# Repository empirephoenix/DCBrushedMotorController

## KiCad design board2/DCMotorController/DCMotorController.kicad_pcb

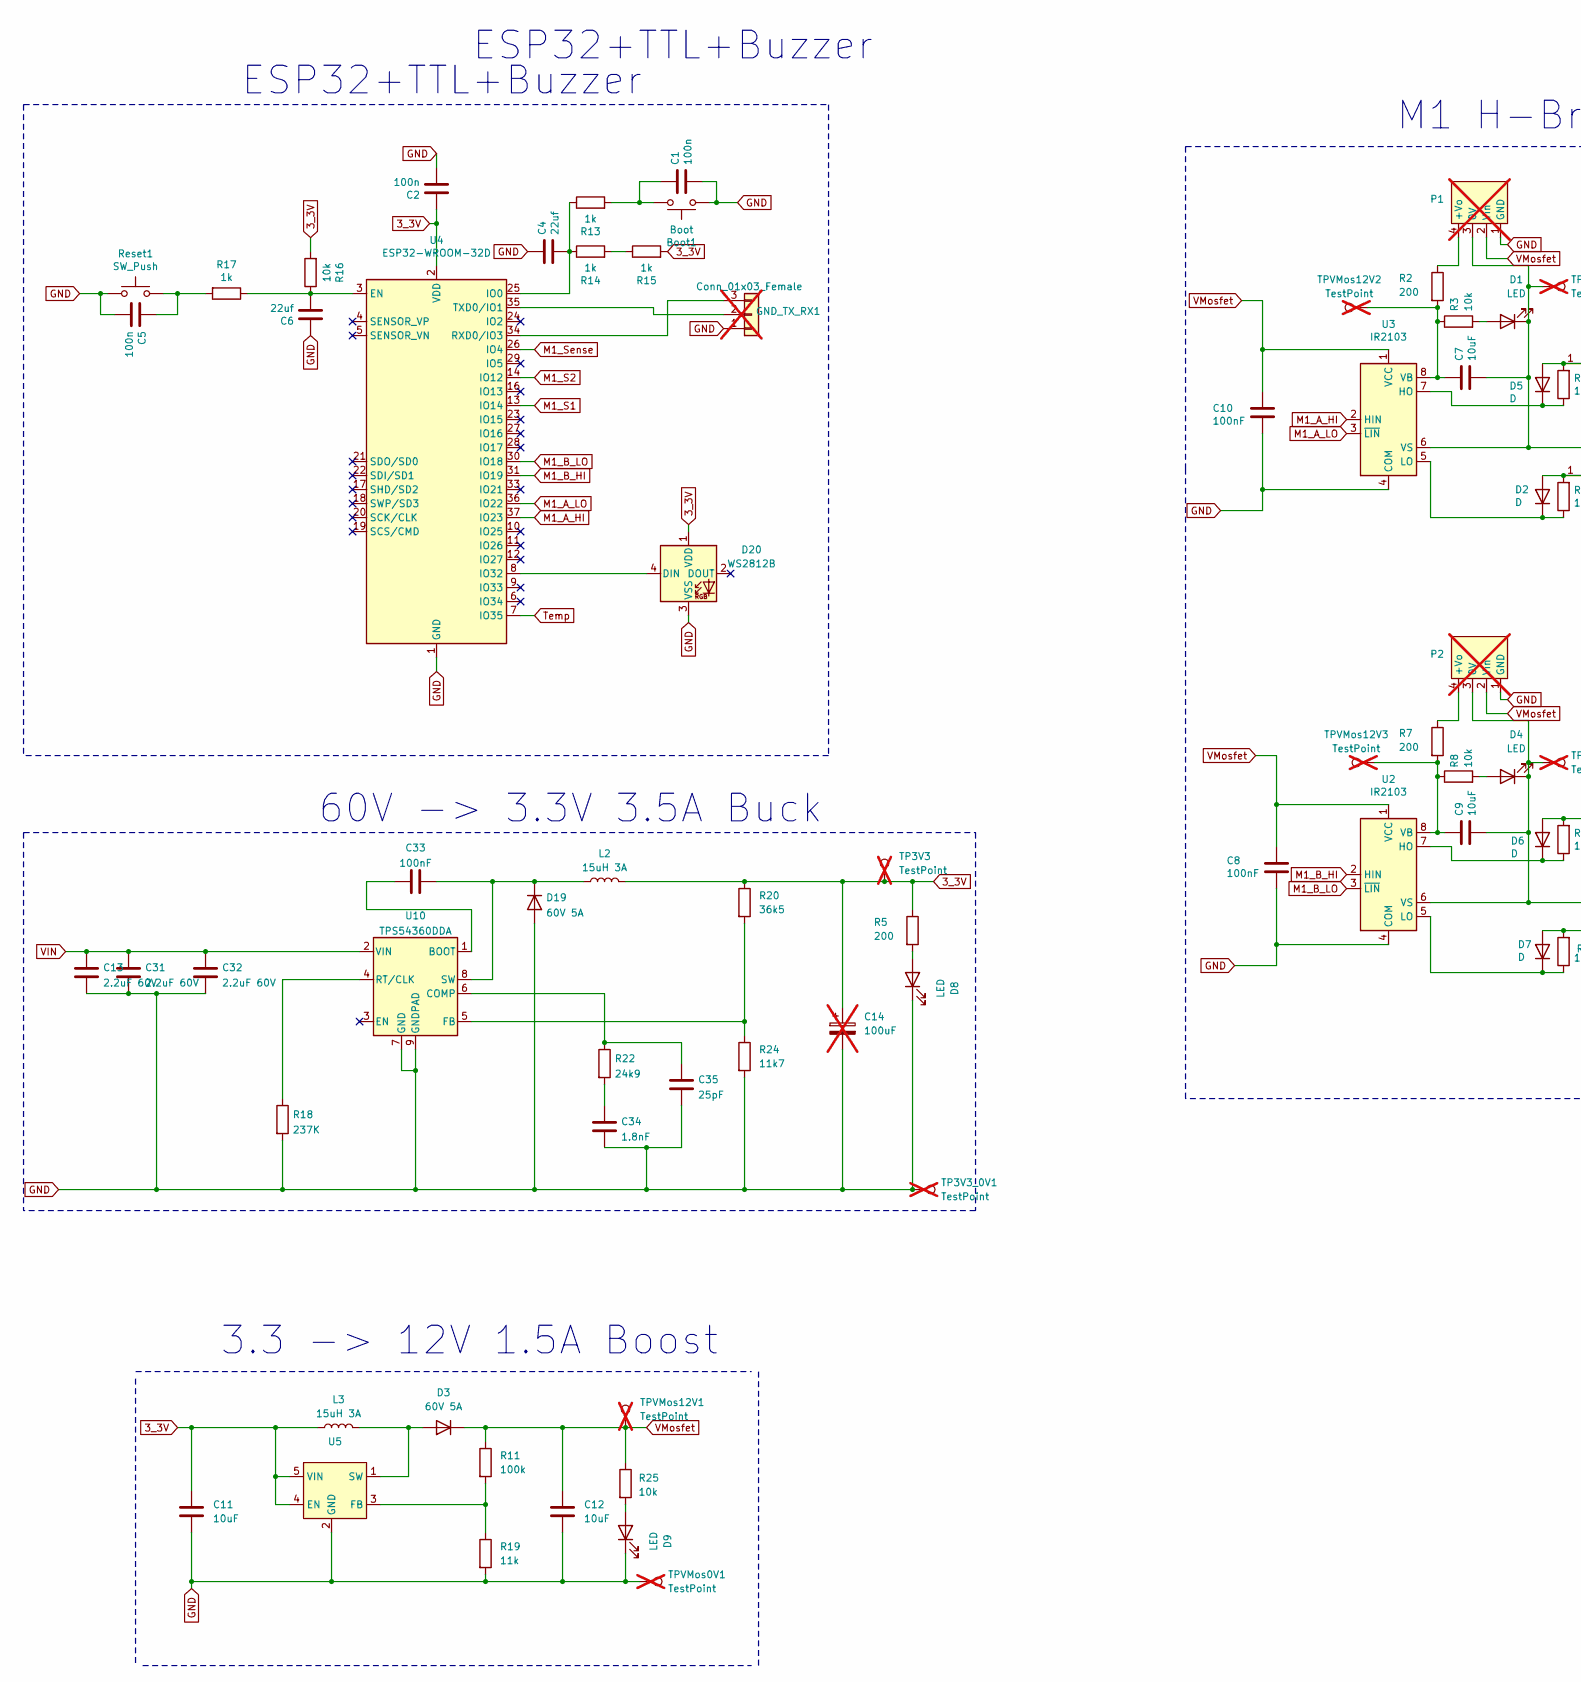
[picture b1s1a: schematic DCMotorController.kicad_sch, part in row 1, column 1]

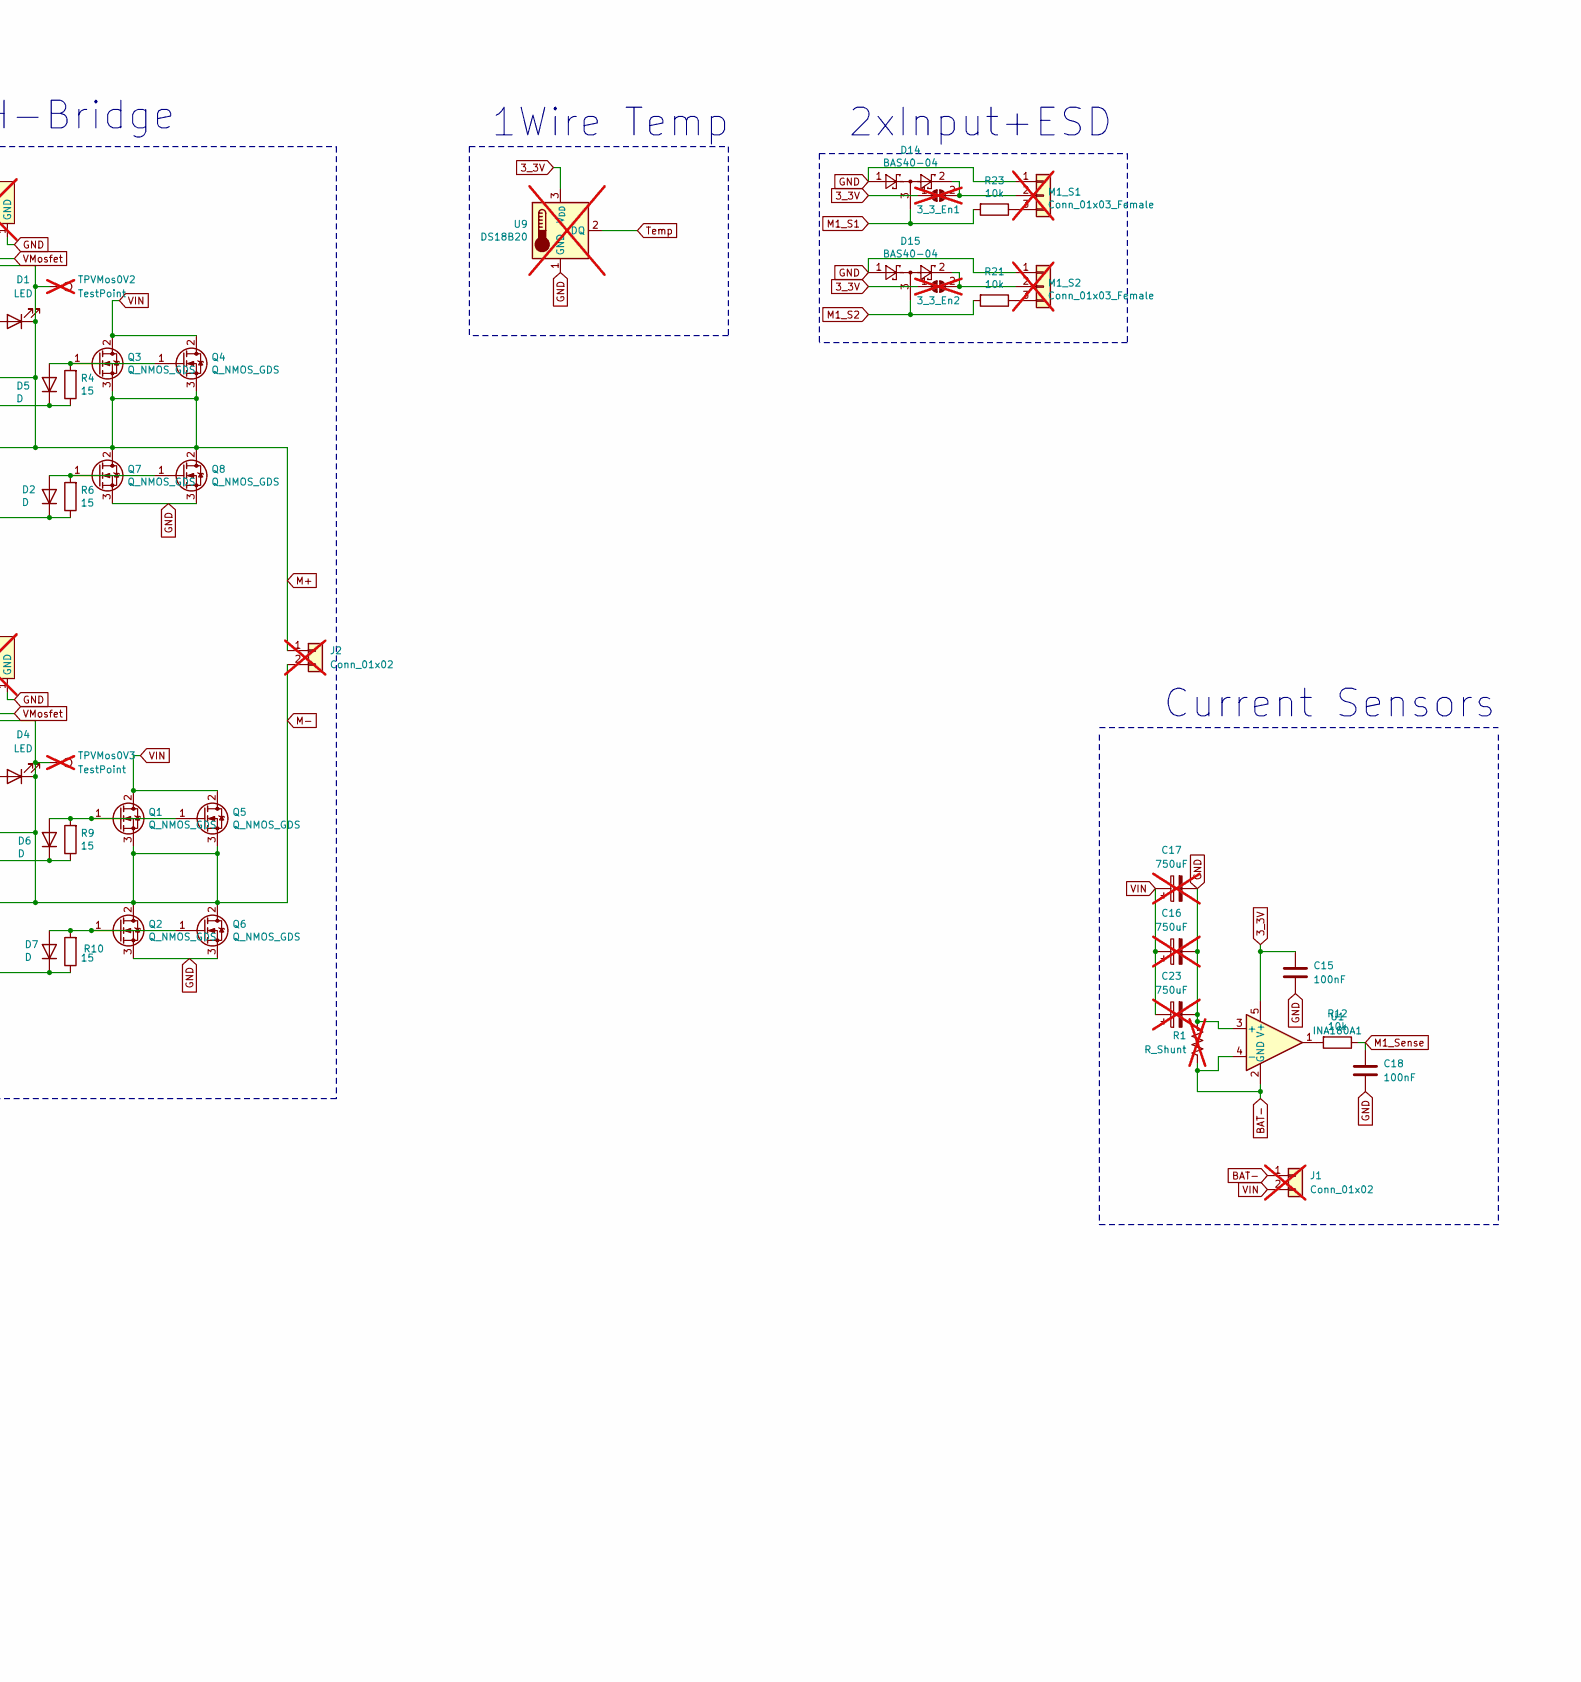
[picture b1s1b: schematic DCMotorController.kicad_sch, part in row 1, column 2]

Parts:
3_3_En1, 3_3_En2: SolderJumper-2_P1.3mm_Open_RoundedPad1.0x1.5mm; not fitted
Boot1: Boot; SW_SPST_CK_RS282G05A3; LCSC C72443
C1, C2, C5: 100n; C_0603_1608Metric; LCSC C14663
C4, C6: 22uf; C_0805_2012Metric; LCSC C5674
C7, C9: 10uF; C_1206_3216Metric; LCSC C13585
C8, C10, C15, C18, C33: 100nF; C_0603_1608Metric; LCSC C14663
C11, C12: 10uF; C_1206_3216Metric
C13, C31, C32: 2.2uF 60V; C_1206_3216Metric; LCSC C920964
C14: 100uF; CP_Radial_D10.0mm_P2.50mm_P5.00mm; not fitted
C16, C17, C23: 750uF; CP_Radial_D12.5mm_P5.00mm; LCSC C316460; not fitted
C34: 1.8nF; C_0603_1608Metric; LCSC C1599
C35: 25pF; C_0603_1608Metric; LCSC C282067
D1, D4, D8, D9: LED; LED_0805_2012Metric
D2, D5, D6, D7: D; D_SOD-123; LCSC C81598
D3, D19: 60V 5A; D_SMA; LCSC C513479
D14, D15: BAS40-04; SOT-23; LCSC C397601
D20: WS2812B; LED_WS2812B_PLCC4_5.0x5.0mm_P3.2mm; LCSC no
GND_TX_RX1: Conn_01x03_Female; PinHeader_1x03_P2.54mm_Vertical; LCSC no; not fitted
J1: Conn_01x02; AMASS_XT60-M_1x02_P7.20mm_Vertical; not fitted
J2: Conn_01x02; AMASS_XT60-F_1x02_P7.20mm_Vertical; not fitted
L2, L3: 15uH 3A; L_10.4x10.4_H4.8; LCSC C151872
M1_S1, M1_S2: Conn_01x03_Female; PinHeader_1x03_P2.54mm_Vertical; LCSC no; not fitted
P1, P2: Converter_DCDC_TRACO_TEA1-xxxx_THT; LCSC C7465190; not fitted
Q1, Q2, Q3, Q4, Q5, Q6, Q7, Q8: Q_NMOS_GDS; TO-252-2; LCSC C110912
R1: R_Shunt; Shunt 1moh 5W; LCSC C695947; not fitted
R2, R5, R7: 200; R_0603_1608Metric; LCSC C25217
R3, R8, R25: 10k; R_0603_1608Metric
R4, R6, R9, R10: 15; R_0603_1608Metric; LCSC C22810
R11: 100k; R_0603_1608Metric; LCSC C22797
R12, R16, R21, R23: 10k; R_0603_1608Metric; LCSC C25804
R13, R14, R15, R17: 1k; R_0603_1608Metric; LCSC C21190
R18: 237K; R_0603_1608Metric_Pad0.98x0.95mm_HandSolder; LCSC C2998117
R19: 11k; R_0603_1608Metric; LCSC C25950
R20: 36k5; R_0603_1608Metric; LCSC C2930095
R22: 24k9; R_0603_1608Metric; LCSC C25962
R24: 11k7; R_0805_2012Metric; LCSC C865154
Reset1: SW_Push; SW_SPST_CK_RS282G05A3; LCSC C72443
TP3V3, TP3V3_0V1: TestPoint; TestPoint_Pad_2.0x2.0mm; not fitted
TPVMos0V1, TPVMos0V2, TPVMos0V3, TPVMos12V1, TPVMos12V2, TPVMos12V3: TestPoint; TestPoint_Pad_2.0x2.0mm; not fitted
U1: INA180A1; SOT-23-5; LCSC C122228
U2, U3: IR2103; SOP-8_3.9x4.9mm_P1.27mm; LCSC C111908
U4: ESP32-WROOM-32D; ESP32-WROOM-32_no_wifi; LCSC C529578
U5: SOT-23-5; LCSC C181744
U9: DS18B20; TO-92_Inline; LCSC lcsc; not fitted
U10: TPS54360DDA; TI_SO-PowerPAD-8_ThermalVias; LCSC C44377

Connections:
3_3V: 3_3_En1.1 (A), 3_3_En2.1 (A), C2.2, C11.1, C14.1, C15.1, D20.1 (VDD), L2.2, L3.1, R5.1, R15.2, R16.2, R20.1, TP3V3.1, U1.5 (V+), U4.2 (VDD), U5.4 (EN), U5.5 (VIN), U9.3 (V_{DD})
BAT-: J1.1, R1.2, U1.2 (GND), U1.4 (-)
GND: Boot1.1, C1.1, C2.1, C4.1, C5.1, C6.1, C8.2, C10.2, C11.2, C12.2, C13.2, C14.2, C15.2, C16.2, C17.2, C18.1, C23.2, C31.2, C32.2, C34.2, C35.2, D8.1 (K), D9.1 (K), D14.1, D15.1, D19.2 (A), D20.3 (VSS), GND_TX_RX1.1, M1_S1.1, M1_S2.1, P1.1 (GND), P2.1 (GND), Q2.3 (S), Q6.3 (S), Q7.3 (S), Q8.3 (S), R1.1, R18.2, R19.2, R24.2, Reset1.1, TP3V3_0V1.1, TPVMos0V1.1, U1.3 (+), U2.4 (COM), U3.4 (COM), U4.1 (GND), U4.15 (GND), U4.38 (GND), U4.39 (GND), U5.2 (GND), U9.1 (GND), U10.7 (GND), U10.9 (GNDPAD)
M1_A_HI: U3.2 (HIN), U4.37 (IO23)
M1_A_LO: U3.3 (~LIN), U4.36 (IO22)
M1_B_HI: U2.2 (HIN), U4.31 (IO19)
M1_B_LO: U2.3 (~LIN), U4.30 (IO18)
M1_S1: D14.3, R23.2, U4.13 (IO14)
M1_S2: D15.3, R21.2, U4.14 (IO12)
M1_Sense: C18.2, R12.1, U4.26 (IO4)
M+: C7.2, D1.1 (K), J2.1, P1.3 (0V), Q3.3 (S), Q4.3 (S), Q7.2 (D), Q8.2 (D), TPVMos0V2.1, U3.6 (VS)
M-: C9.2, D4.1 (K), J2.2, P2.3 (0V), Q1.3 (S), Q2.2 (D), Q5.3 (S), Q6.2 (D), TPVMos0V3.1, U2.6 (VS)
unnamed: 3_3_En1.2 (B), D14.2, M1_S1.2
unnamed: 3_3_En2.2 (B), D15.2, M1_S2.2
unnamed: Boot1.2, C1.2, R13.2
unnamed: C5.2, R17.2, Reset1.2
unnamed: C34.1, R22.2
unnamed: D1.2 (A), R3.2
unnamed: D2.2 (A), Q7.1 (G), Q8.1 (G), R6.2
unnamed: D2.1 (K), R6.1, U3.5 (LO)
unnamed: D3.2 (A), L3.2, U5.1 (SW)
unnamed: D4.2 (A), R8.2
unnamed: D5.2 (A), Q3.1 (G), Q4.1 (G), R4.2
unnamed: D5.1 (K), R4.1, U3.7 (HO)
unnamed: D6.2 (A), Q1.1 (G), Q5.1 (G), R9.2
unnamed: D6.1 (K), R9.1, U2.7 (HO)
unnamed: D7.2 (A), Q2.1 (G), Q6.1 (G), R10.2
unnamed: D7.1 (K), R10.1, U2.5 (LO)
unnamed: D8.2 (A), R5.2
unnamed: D9.2 (A), R25.2
unnamed: C33.2, D19.1 (K), L2.1, U10.8 (SW)
unnamed: D20.4 (DIN), U4.8 (IO32)
unnamed: GND_TX_RX1.2, U4.35 (TXD0/IO1)
unnamed: GND_TX_RX1.3, U4.34 (RXD0/IO3)
unnamed: M1_S1.3, R23.1
unnamed: M1_S2.3, R21.1
unnamed: P1.4 (+Vo), R2.1
unnamed: P2.4 (+Vo), R7.1
unnamed: R12.2, U1.1
unnamed: R14.2, R15.1
unnamed: C9.1, R7.2, R8.1, TPVMos12V3.1, U2.8 (VB)
unnamed: C7.1, R2.2, R3.1, TPVMos12V2.1, U3.8 (VB)
unnamed: C6.2, R16.1, R17.1, U4.3 (EN)
unnamed: C4.2, R13.1, R14.1, U4.25 (IO0)
unnamed: R11.2, R19.1, U5.3 (FB)
unnamed: C33.1, U10.1 (BOOT)
unnamed: C35.1, R22.1, U10.6 (COMP)
unnamed: R20.2, R24.1, U10.5 (FB)
unnamed: R18.1, U10.4 (RT/CLK)
Temp: U4.7 (IO35), U9.2 (DQ)
VIN: C13.1, C16.1, C17.1, C23.1, C31.1, C32.1, J1.2, Q1.2 (D), Q3.2 (D), Q4.2 (D), Q5.2 (D), U10.2 (VIN)
VMosfet: C8.1, C10.1, C12.1, D3.1 (K), P1.2 (Vin), P2.2 (Vin), R11.1, R25.1, TPVMos12V1.1, U2.1 (VCC), U3.1 (VCC)

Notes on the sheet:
Current Sensors
3.3 -> 12V 1.5A Boost
60V -> 3.3V 3.5A Buck
ESP32+TTL+Buzzer
1Wire Temp
2xInput+ESD
M1 H-Bridge

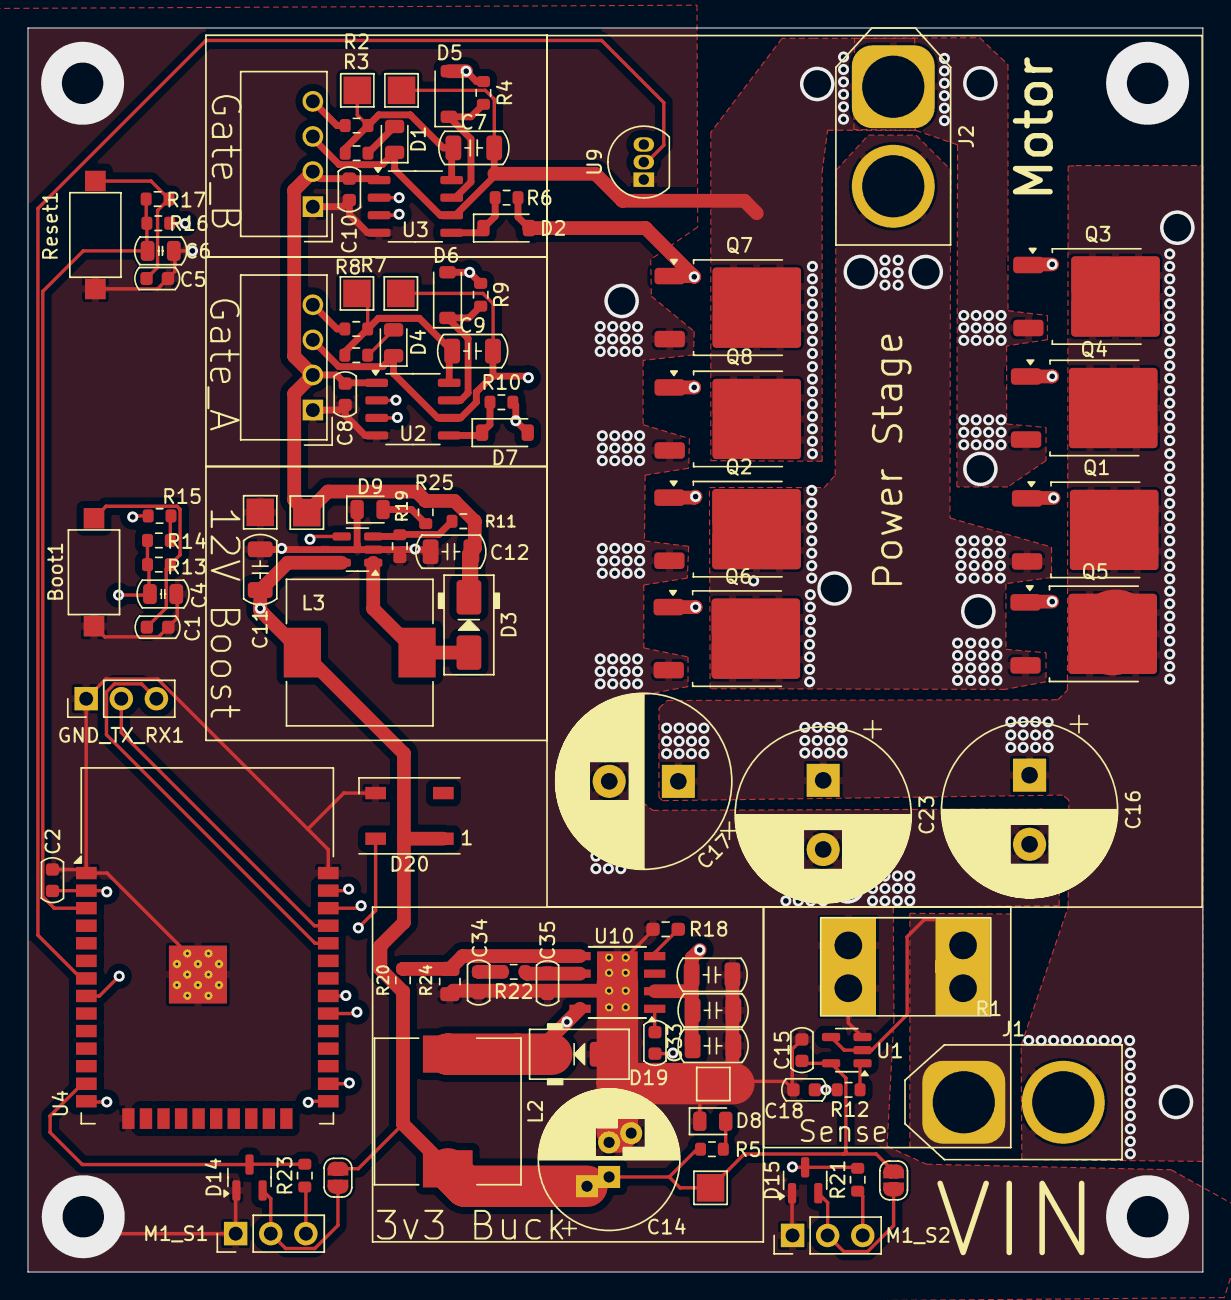
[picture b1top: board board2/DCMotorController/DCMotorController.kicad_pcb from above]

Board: 4 copper layers, 85.0 x 90.0 mm, 97 parts (0 on the bottom side), 52 nets.

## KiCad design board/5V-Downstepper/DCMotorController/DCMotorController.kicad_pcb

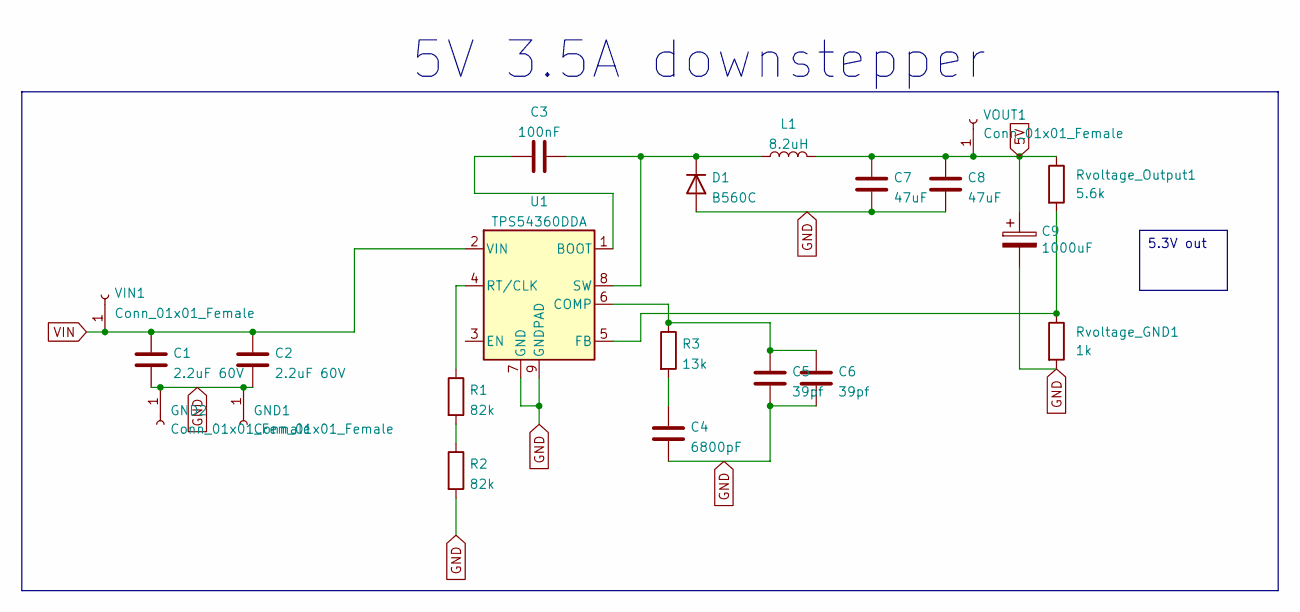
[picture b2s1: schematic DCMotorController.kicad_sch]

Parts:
C1, C2: 2.2uF 60V; C_1206_3216Metric; LCSC C920964
C3: 100nF; C_0603_1608Metric; LCSC C14663
C4: 6800pF; C_0603_1608Metric; LCSC C1631
C5, C6: 39pf; C_0603_1608Metric; LCSC C1666
C7, C8: 47uF; C_1206_3216Metric; LCSC C96123
C9: 1000uF; CP_Radial_D10.0mm_P5.00mm; LCSC C503217
D1: B560C; D_SMC_Handsoldering; LCSC C85100
GND1, GND2: Conn_01x01_Female; 60A_Wire_solder
L1: 8.2uH; L_12x12mm_H8mm; LCSC C2761921
R1, R2: 82k; R_0603_1608Metric_Pad0.98x0.95mm_HandSolder; LCSC C23254
R3: 13k; R_0603_1608Metric; LCSC C22797
Rvoltage_GND1: 1k; R_0603_1608Metric
Rvoltage_Output1: 5.6k; R_0603_1608Metric
U1: TPS54360DDA; TI_SO-PowerPAD-8_ThermalVias; LCSC C44377
VIN1: Conn_01x01_Female; 60A_Wire_solder
VOUT1: Conn_01x01_Female; 60A_Wire_solder

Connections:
5V: C7.1, C8.1, C9.1, L1.2, Rvoltage_Output1.1, VOUT1.1
GND: C1.2, C2.2, C4.2, C5.2, C6.2, C7.2, C8.2, C9.2, D1.2 (A), GND1.1, GND2.1, R2.2, Rvoltage_GND1.2, U1.7 (GND), U1.9 (GNDPAD)
unnamed: C3.1, U1.1 (BOOT)
unnamed: C3.2, D1.1 (K), L1.1, U1.8 (SW)
unnamed: C4.1, R3.2
unnamed: C5.1, C6.1, R3.1, U1.6 (COMP)
unnamed: R1.1, U1.4 (RT/CLK)
unnamed: R1.2, R2.1
unnamed: Rvoltage_GND1.1, Rvoltage_Output1.2, U1.5 (FB)
VIN: C1.1, C2.1, U1.2 (VIN), VIN1.1

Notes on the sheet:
5.3V out
5V 3.5A downstepper

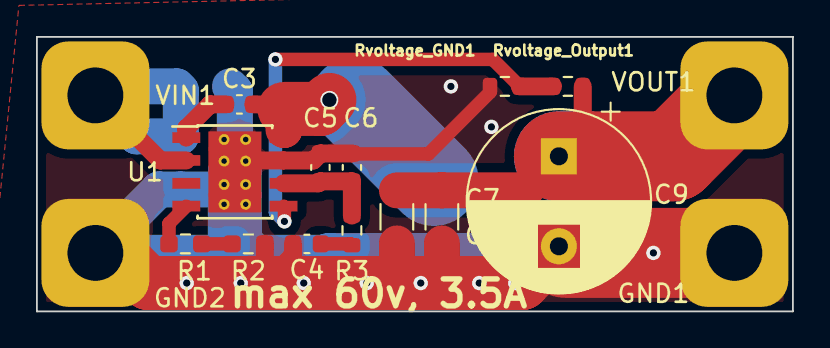
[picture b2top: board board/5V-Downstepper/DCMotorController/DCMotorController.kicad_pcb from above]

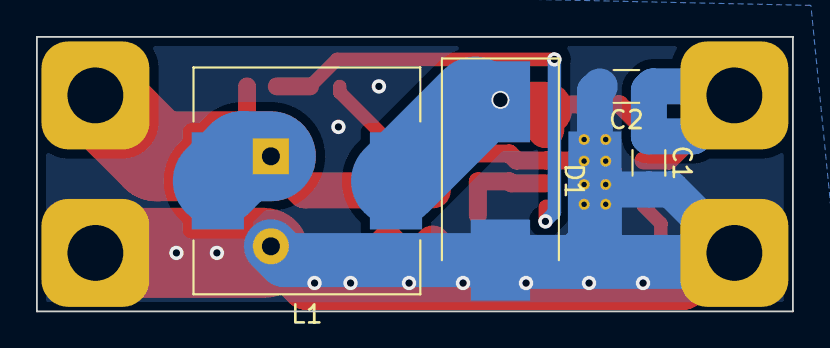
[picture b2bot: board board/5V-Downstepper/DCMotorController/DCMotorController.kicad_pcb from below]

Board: 2 copper layers, 42.0 x 15.2 mm, 21 parts (4 on the bottom side), 10 nets.

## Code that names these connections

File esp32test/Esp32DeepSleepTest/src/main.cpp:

#include <Arduino.h>
#include <Adafruit_NeoPixel.h>
#include "joy_rmt_rc.h"
#include "RunningMedian.h"
#include <OneWire.h>
#include <DallasTemperature.h>

// pin setup
#define LED_STATUS 32
#define ONE_WIRE_BUS 35

#define M1_SENSE 4

#define IN1 14
#define IN2 12

#define M1_A_LO 22
#define M1_A_HI 23
#define M1_B_LO 18
#define M1_B_HI 19

#define freq 6000
#define resolution 8

// Configuration
#define SHUNT_MOHM 2
#define MAX_AVG_CURRENT 15000
#define MAX_SPIKE_CURRENT 60000
#define NULL_PASS_DELAY 50

#define mode 0
#define turningMod 0

#define deadzoneMinCH1 1480
#define deadzoneMaxCH1 1520
#define minCH1 950
#define maxCH1 2050

#define minTEMPC -30
#define maxTEMPC 60

// constants
#define STATE_WAIT_NEUTRAL 0
#define STATE_DEFAULT 1
#define STATE_ERROR -1

#define FOREACH_INPUT(INPUT) \
  INPUT(NONE)                \
  INPUT(RC)                  \
  INPUT(VOLTAGE)

#define GENERATE_ENUM(ENUM) ENUM,
#define GENERATE_STRING(STRING) #STRING,

enum INPUT_MODE
{
  FOREACH_INPUT(GENERATE_ENUM)
};

Adafruit_NeoPixel pixels(1, LED_STATUS, NEO_GRBW);

float lastPower;
float nullPass;

const int M1_A_CHANNEL = 0;
const int M1_B_CHANNEL = 1;

RunningMedian m1 = RunningMedian(10);
long m1_last = 0;
  int state = STATE_WAIT_NEUTRAL;

// Configure RMT peripheral for each RC channel
RingbufHandle_t ringbuffers[axis_count];

void check(bool value, char *output)
{
  if (value)
  {
    printf(output);
  }
}

void setup()
{
  lastPower = 0;
  Serial.begin(115200);

  pinMode(IN1, INPUT);
  pinMode(IN2, INPUT);

  pinMode(M1_A_LO, OUTPUT);
  pinMode(M1_A_HI, OUTPUT);
  pinMode(M1_B_LO, OUTPUT);
  pinMode(M1_B_HI, OUTPUT);
 
  yield();
  
  pixels.begin();
  pixels.setPixelColor(0, pixels.Color(0, 10, 0));
  pixels.show();
  Serial.println("Start done");

  pixels.setPixelColor(0, pixels.Color(100, 0, 0));
  pixels.show();


  ledcSetup(M1_A_CHANNEL, freq, resolution);
  ledcAttachPin(M1_A_HI, M1_A_CHANNEL);
  ledcSetup(M1_B_CHANNEL, freq, resolution);
  ledcAttachPin(M1_B_HI, M1_B_CHANNEL);

  esp_err_t er = ESP_OK;
  for (int i = 0; i < axis_count; i++)
  {
    rmt_config_t rmt_rx_config = {};
    rmt_rx_config.rmt_mode = RMT_MODE_RX;
    rmt_rx_config.channel = rc_channels[i].channel;
    rmt_rx_config.clk_div = rmt_clock_divider;
    rmt_rx_config.gpio_num = rc_channels[i].pin;
    rmt_rx_config.mem_block_num = 1;
    rmt_rx_config.rx_config.filter_en = true;
    rmt_rx_config.rx_config.filter_ticks_thresh = rmt_filter_threshold;
    rmt_rx_config.rx_config.idle_threshold = rmt_idle_threshold;

    er = rmt_config(&rmt_rx_config);
    check(ESP_OK != er, "ERROR: rmt_config failed\n");

    er = rmt_driver_install(rc_channels[i].channel, 1024, 0);
    check(ESP_OK != er, "ERROR: rmt_driver_install failed\n");

    er = rmt_get_ringbuf_handle(rc_channels[i].channel, &(ringbuffers[i]));
    check(ESP_OK != er, "ERROR: rmt_get_ringbuf_handle failed\n");
    check(NULL == ringbuffers[i], "ERROR: rmt_get_ringbuf_handle gave a NULL handle\n");

    er = rmt_rx_start(rc_channels[i].channel, true);
    check(ESP_OK != er, "ERROR: rmt_rx_start failed\n");
  }

  pixels.setPixelColor(0, pixels.Color(0, 0, 100));
  pixels.show();
}

float mapfloat(float x, float in_min, float in_max, float out_min, float out_max)
{
  return (x - in_min) * (out_max - out_min) / (in_max - in_min) + out_min;
}

void joy_rmt_rc_read_task()
{

  // Read loop
  size_t length = 0;
  rmt_item32_t *items = NULL;
  uint32_t duration;
  for (int i = 0; i < axis_count; i++)
  {
    duration = 0;
    items = (rmt_item32_t *)xRingbufferReceive(ringbuffers[i], &length, 1);
    if (NULL != items)
    {
      // Convert length from number of bytes to number of entries
      length /= sizeof(rmt_item32_t);

      // Read high period of most recent data point
      rmt_item32_t recent = items[length - 1];
      if (0 != recent.level0)
      {
        duration = recent.duration0;
      }
      else if (0 != recent.level1)
      {
        duration = recent.duration1;
      }

      // Return memory to ring buffer
      vRingbufferReturnItem(ringbuffers[i], (void *)items);

      // Clamp between min & max
      if (duration < rc_receive_min)
      {
        continue;
      }
      else if (duration > rc_receive_max)
      {
        continue;
      }

      if (i == 0)
      {
        m1.add(duration);
        m1_last = millis();
      }
    }
  }
}

bool waitforNeutral(float tempC)
{

  float m1v = m1.getAverage();

  int ok = 0;
  boolean neutral = m1v > deadzoneMinCH1 && m1v < deadzoneMaxCH1;
  boolean tempReady = ok == 1 && tempC > minTEMPC || tempC < maxTEMPC;

  Serial.print("Channel is at ");
  Serial.print(m1v);
  Serial.print(" and temperature ");
  Serial.print(tempC);
  Serial.println("°C");
    

  if (neutral && tempReady)
  {
    Serial.print("Precheck ok");
    pixels.setPixelColor(0, pixels.Color(0, 0, 200));
    pixels.show();
    delay(100);
    return true;   
  }

  if (!tempReady){
    Serial.print("Invalid Temperature");
    pixels.setPixelColor(0, pixels.Color(50, 50, 50));
  }
  if (!neutral) {
    Serial.print("Not neutral");
      pixels.setPixelColor(0, pixels.Color(200, 0, 0));
  }
      
  pixels.show();
  return false;  
}

float handleMotor(float ratio, int high_channel_a_ledc, int low_pin_a, int high_channel_b_ledc, int low_pin_b)
{
  if (nullPass > millis())
  {
    return 0;
  }

  float oldPower = lastPower;
  lastPower = ratio;
  Serial.print(oldPower);
  Serial.print(" ");
  Serial.println(ratio);
  if (oldPower <= 0 && ratio > 0)
  {
    digitalWrite(low_pin_a, LOW);
    digitalWrite(low_pin_b, LOW);
    ledcWrite(high_channel_a_ledc, 0);
    ledcWrite(high_channel_b_ledc, 0);
    Serial.print("Null pass delay");
    nullPass = millis() + NULL_PASS_DELAY;
    return 0;
  }
  if (oldPower >= 0 && ratio < 0)
  {
    digitalWrite(low_pin_a, LOW);
    digitalWrite(low_pin_b, LOW);
    ledcWrite(high_channel_a_ledc, 0);
    ledcWrite(high_channel_b_ledc, 0);
    Serial.println("Null pass delay");
    nullPass = millis() + NULL_PASS_DELAY;
    return 0;
  }

  if (ratio > 0)
  {
    int forward = mapfloat(ratio, 0, 1, 0, 255);
    digitalWrite(low_pin_a, LOW);
    digitalWrite(low_pin_b, HIGH);
    ledcWrite(high_channel_a_ledc, forward);
    ledcWrite(high_channel_b_ledc, 0);

    return forward;
  }
  else
  {
    int reverse = mapfloat(ratio, -1, 0, 255, 0);
    digitalWrite(low_pin_a, HIGH);
    digitalWrite(low_pin_b, LOW);
    ledcWrite(high_channel_a_ledc, 0);
    ledcWrite(high_channel_b_ledc, reverse);
    return reverse;
  }
}

uint32_t calculateCurrentSpike(uint32_t current, float powerByte)
{
  if (powerByte < 5)
  {
    return 0;
  }
  return current * 255 / powerByte;
}

void defaultMode(float ch1)
{
  float power1 = 0;
  float power2 = 0;
#if (mode == 0)
  power1 = handleMotor(ch1, M1_A_CHANNEL, M1_A_LO, M1_B_CHANNEL, M1_B_LO);

#elif (mode == 1)
  float brake = 1 - abs(ch2);
  float brakeFactor = brake * turningMod + (1 - turningMod);

  float left = ch1;
  float right = ch1;
  if (ch2 < 0)
  {
    left = left * brakeFactor;
  }
  else
  {
    right = right * brakeFactor;
  }
  power1 = handleMotor(1, left, M1_A_CHANNEL, M1_A_LO, M1_B_CHANNEL, M1_B_LO);
  power2 = handleMotor(2, right, M2_A_CHANNEL, M2_A_LO, M2_B_CHANNEL, M2_B_LO);
#endif

  uint32_t raw_cur =    (M1_SENSE);
  uint32_t cur1_ma = raw_cur * 1000 / 50 / SHUNT_MOHM;
  uint32_t cur1_spike_ma = calculateCurrentSpike(cur1_ma, power1);

  if (cur1_ma > MAX_AVG_CURRENT)
  {
    state = STATE_ERROR;
    Serial.print("M1 reached current limit average");
    Serial.println(cur1_ma);
    Serial.flush();
    return;
  }

  if (cur1_spike_ma > MAX_SPIKE_CURRENT)
  {
    state = STATE_ERROR;
    Serial.print("M1 reached current limit spike");
    Serial.println(cur1_spike_ma);
    Serial.flush();
    return;
  }

  pixels.setPixelColor(0, pixels.Color(0, power1, power2));
  Serial.print("power1 ");
  Serial.print(power1);
  Serial.print(" cur1Ma:");
  Serial.print(cur1_ma);
  Serial.print(" cur1Maspike:");
  Serial.print(cur1_spike_ma);
}

void loop()
{

  joy_rmt_rc_read_task();
  float tempC = 30;

  if (state == STATE_WAIT_NEUTRAL || state == STATE_ERROR)
  {
    if (state == STATE_ERROR) {
      handleMotor(0, M1_A_CHANNEL, M1_A_LO, M1_B_CHANNEL, M1_B_LO);
      pixels.setPixelColor(0, pixels.Color(255, 0, 0, 10));
      pixels.show();
    }
    if (waitforNeutral(tempC)){
      state = STATE_DEFAULT;
    }
    return;
  }

  long curTime = millis();
  if (curTime - m1_last > 200)
  {
    Serial.println("Missing signal for m1, error");
    Serial.flush();
    state = STATE_ERROR;
  }

  if (tempC > maxTEMPC)
  {
    state = STATE_ERROR;
  }

  float m1Raw = m1.getAverage();

  float ch1 = 0;
  if (m1Raw < deadzoneMinCH1 || m1Raw > deadzoneMaxCH1)
  {
    ch1 = mapfloat(m1Raw, minCH1, maxCH1, -1, 1);
    ch1 = constrain(ch1, -1, 1);
  }
  if (state == STATE_DEFAULT)
  {
    defaultMode(ch1);
  }
  pixels.show();
}

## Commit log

2022-01-07 initial version
2022-02-04 first version + test firmeware
2022-02-12 txMenu test
2022-02-14 rmt rc receiver test
2022-06-22 simple 2 channel forward backword controll with smoothing
2022-08-12 Allegro current sensor edition
2022-08-12 added voltage converter
2022-12-28 updated with newer 5 and 3 v supply, potentiometer supply optional added, current sensor rearangement
2023-05-05 update to newer current sensoring
2023-05-12 clamp range extended slightly, fixed 100% duty cycle discharging high side capacitor
2023-06-16 testing
2023-06-16 added ignore
2023-06-17 adjusted voltage divider for tps
2024-06-16 v2 ordering
2024-07-11 add board2 firemware update
2024-08-04 fix temp check wrong
2024-08-04 less smoothing, fix current sense pin
